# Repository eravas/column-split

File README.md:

# column-split
a columnar, split, tkl keyboard

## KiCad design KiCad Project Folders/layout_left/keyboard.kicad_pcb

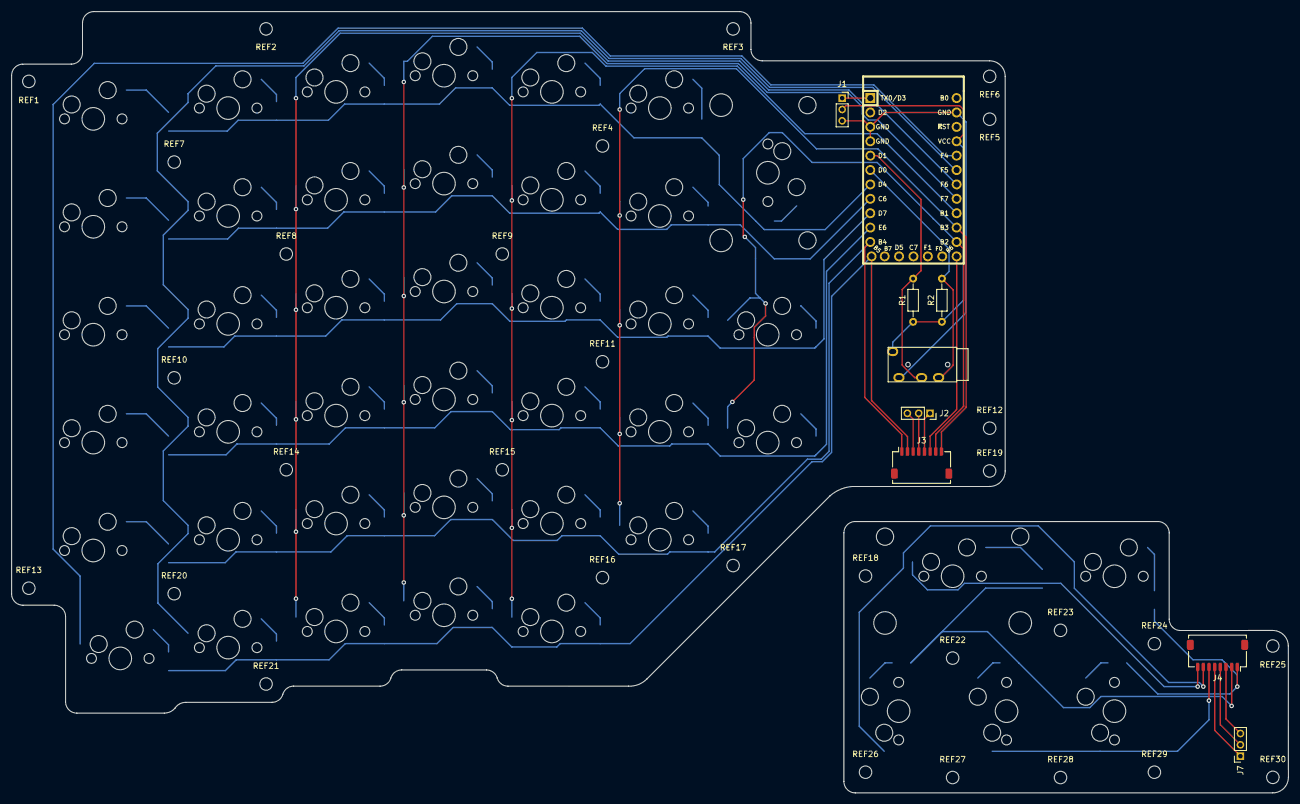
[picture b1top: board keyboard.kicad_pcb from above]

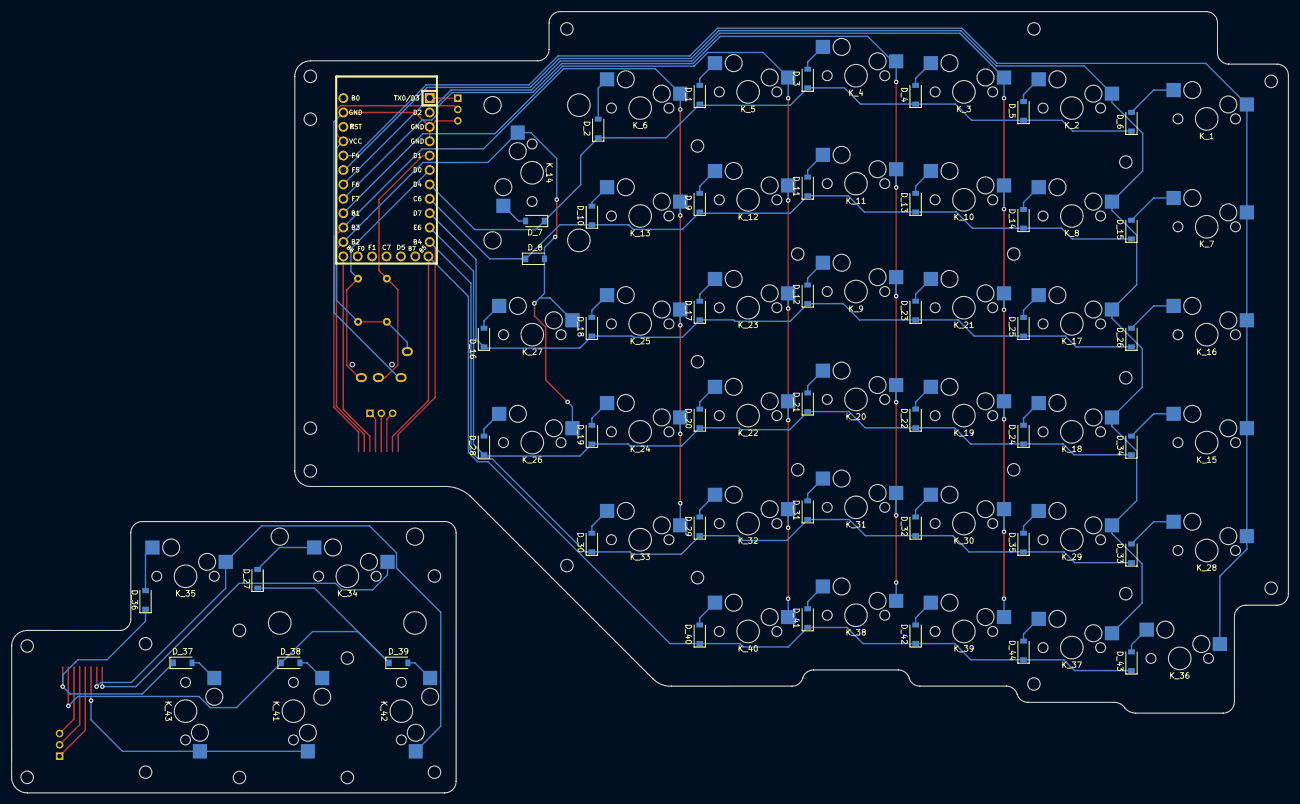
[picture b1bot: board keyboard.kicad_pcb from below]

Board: 2 copper layers, 225.4 x 137.9 mm, 126 parts (44 on the bottom side), 65 nets.

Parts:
D_1, D_2, D_3, D_4, D_5, D_6, D_7, D_8, D_9, D_10, D_11, D_12, D_13, D_14, D_15, D_16, D_17, D_18, D_19, D_20, D_21, D_22, D_23, D_24, D_25, D_26, D_27, D_28, D_29, D_30, D_31, D_32, D_33, D_34, D_35, D_36, D_37, D_38, D_39, D_40, D_41, D_42, D_43, D_44: D; D_SOD-123
J1, J2, J7: Conn_01x03_Female; PinSocket_1x03_P2.00mm_Vertical
J3, J4: Conn_01x08_Female; Molex_Pico-Clasp_202396-0807_1x08-1MP_P1.00mm_Horizontal
K_1, K_7, K_15, K_16, K_28, K_41, K_42, K_43: KEYSW; MXOnly-1.5U-Hotswap
K_2, K_3, K_4, K_5, K_6, K_8, K_9, K_10, K_11, K_12, K_13, K_17, K_18, K_19, K_20, K_21, K_22, K_23, K_24, K_25, K_26, K_27, K_29, K_30, K_31, K_32, K_33, K_35, K_36, K_37, K_38, K_39, K_40: KEYSW; MXOnly-1U-Hotswap
K_14, K_34: KEYSW; MXOnly-2U-Hotswap
R1, R2: 1k; R_Axial_DIN0204_L3.6mm_D1.6mm_P7.62mm_Horizontal
REF1, REF2, REF3, REF4, REF5, REF6, REF7, REF8, REF9, REF10, REF11, REF12, REF13, REF14, REF15, REF16, REF17, REF18, REF19, REF20, REF21, REF22, REF23, REF24, REF25, REF26, REF27, REF28, REF29, REF30: MountingHole_2.2mm_M2
U1: Elite-C
U2: TRRS; TRRS-PJ-320A

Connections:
GND: J3.3, U1.2 (TIP), U2.2 (TIP)
unnamed: D_1.2 (A), K_1.2 (ROW)
unnamed: D_2.2 (A), K_2.2 (ROW)
unnamed: D_3.2 (A), K_3.2 (ROW)
unnamed: D_4.2 (A), K_4.2 (ROW)
unnamed: D_5.2 (A), K_5.2 (ROW)
unnamed: D_6.2 (A), K_6.2 (ROW)
unnamed: D_7.2 (A), K_7.2 (ROW)
unnamed: D_8.2 (A), K_8.2 (ROW)
unnamed: D_9.2 (A), K_9.2 (ROW)
unnamed: D_10.2 (A), K_10.2 (ROW)
unnamed: D_11.2 (A), K_11.2 (ROW)
unnamed: D_12.2 (A), K_12.2 (ROW)
unnamed: D_13.2 (A), K_13.2 (ROW)
unnamed: D_14.2 (A), K_14.2 (ROW)
unnamed: D_15.2 (A), K_15.2 (ROW)
unnamed: D_16.2 (A), K_16.2 (ROW)
unnamed: D_17.2 (A), K_17.2 (ROW)
unnamed: D_18.2 (A), K_18.2 (ROW)
unnamed: D_19.2 (A), K_19.2 (ROW)
unnamed: D_20.2 (A), K_20.2 (ROW)
unnamed: D_21.2 (A), K_21.2 (ROW)
unnamed: D_22.2 (A), K_22.2 (ROW)
unnamed: D_23.2 (A), K_23.2 (ROW)
unnamed: D_24.2 (A), K_24.2 (ROW)
unnamed: D_25.2 (A), K_25.2 (ROW)
unnamed: D_26.2 (A), K_26.2 (ROW)
unnamed: D_27.2 (A), K_27.2 (ROW)
unnamed: D_28.2 (A), K_28.2 (ROW)
unnamed: D_29.2 (A), K_29.2 (ROW)
unnamed: D_30.2 (A), K_30.2 (ROW)
unnamed: D_31.2 (A), K_31.2 (ROW)
unnamed: D_32.2 (A), K_32.2 (ROW)
unnamed: D_33.2 (A), K_33.2 (ROW)
unnamed: D_34.2 (A), K_34.2 (ROW)
unnamed: D_35.2 (A), K_35.2 (ROW)
unnamed: D_36.2 (A), D_44.2 (A), K_36.2 (ROW)
unnamed: D_37.2 (A), D_43.2 (A), K_37.2 (ROW)
unnamed: D_38.2 (A), K_38.2 (ROW)
unnamed: D_39.2 (A), K_39.2 (ROW)
unnamed: D_40.2 (A), K_40.2 (ROW)
unnamed: D_41.2 (A), K_41.2 (ROW)
unnamed: D_42.2 (A), K_42.2 (ROW), K_43.2 (ROW)
SCL: R2.1, U1.4 (RING2), U2.4 (RING2)
SDA: R1.1, U1.3 (RING1), U2.3 (RING1)
Vcc: J3.2, R1.2, R2.2, U1.1 (SLEEVE), U2.1 (SLEEVE)
Vss_b: J1.3, J4.3
Vss_t: J2.3, J7.3
co6_t: K_39.1 (COL), K_40.1 (COL)
co7_t: K_41.1 (COL), K_42.1 (COL), K_43.1 (COL)
col0: K_5.1 (COL), K_12.1 (COL), K_18.1 (COL), K_25.1 (COL), K_32.1 (COL), K_37.1 (COL)
col1: K_3.1 (COL), K_10.1 (COL), K_16.1 (COL), K_23.1 (COL), K_30.1 (COL), K_36.1 (COL)
col2: K_1.1 (COL), K_8.1 (COL), K_14.1 (COL), K_21.1 (COL), K_28.1 (COL), K_34.1 (COL)
col3: K_7.1 (COL), K_13.1 (COL), K_20.1 (COL), K_27.1 (COL), K_33.1 (COL)
col4: K_2.1 (COL), K_9.1 (COL), K_15.1 (COL), K_22.1 (COL), K_29.1 (COL), K_35.1 (COL)
col5: K_4.1 (COL), K_11.1 (COL), K_17.1 (COL), K_24.1 (COL), K_31.1 (COL)
col6: K_6.1 (COL), K_19.1 (COL), K_26.1 (COL)
ro4_t: D_39.1 (K), D_42.1 (K), J2.1
ro5_t: D_38.1 (K), D_40.1 (K), D_41.1 (K), J2.2
row0: D_1.1 (K), D_2.1 (K), D_3.1 (K), D_4.1 (K), D_5.1 (K), D_6.1 (K)
row1: D_7.1 (K), D_8.1 (K), D_9.1 (K), D_10.1 (K), D_11.1 (K), D_12.1 (K)
row2: D_13.1 (K), D_14.1 (K), D_15.1 (K), D_16.1 (K), D_17.1 (K), D_18.1 (K), D_19.1 (K)
row3: D_20.1 (K), D_21.1 (K), D_22.1 (K), D_23.1 (K), D_24.1 (K), D_25.1 (K), D_26.1 (K)
row4: D_27.1 (K), D_28.1 (K), D_29.1 (K), D_30.1 (K), D_31.1 (K), D_32.1 (K), J1.1
row5: D_33.1 (K), D_34.1 (K), D_35.1 (K), D_36.1 (K), D_37.1 (K), D_43.1 (K), D_44.1 (K), J1.2

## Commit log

2022-03-06 init
    uploading initial designs + notes
